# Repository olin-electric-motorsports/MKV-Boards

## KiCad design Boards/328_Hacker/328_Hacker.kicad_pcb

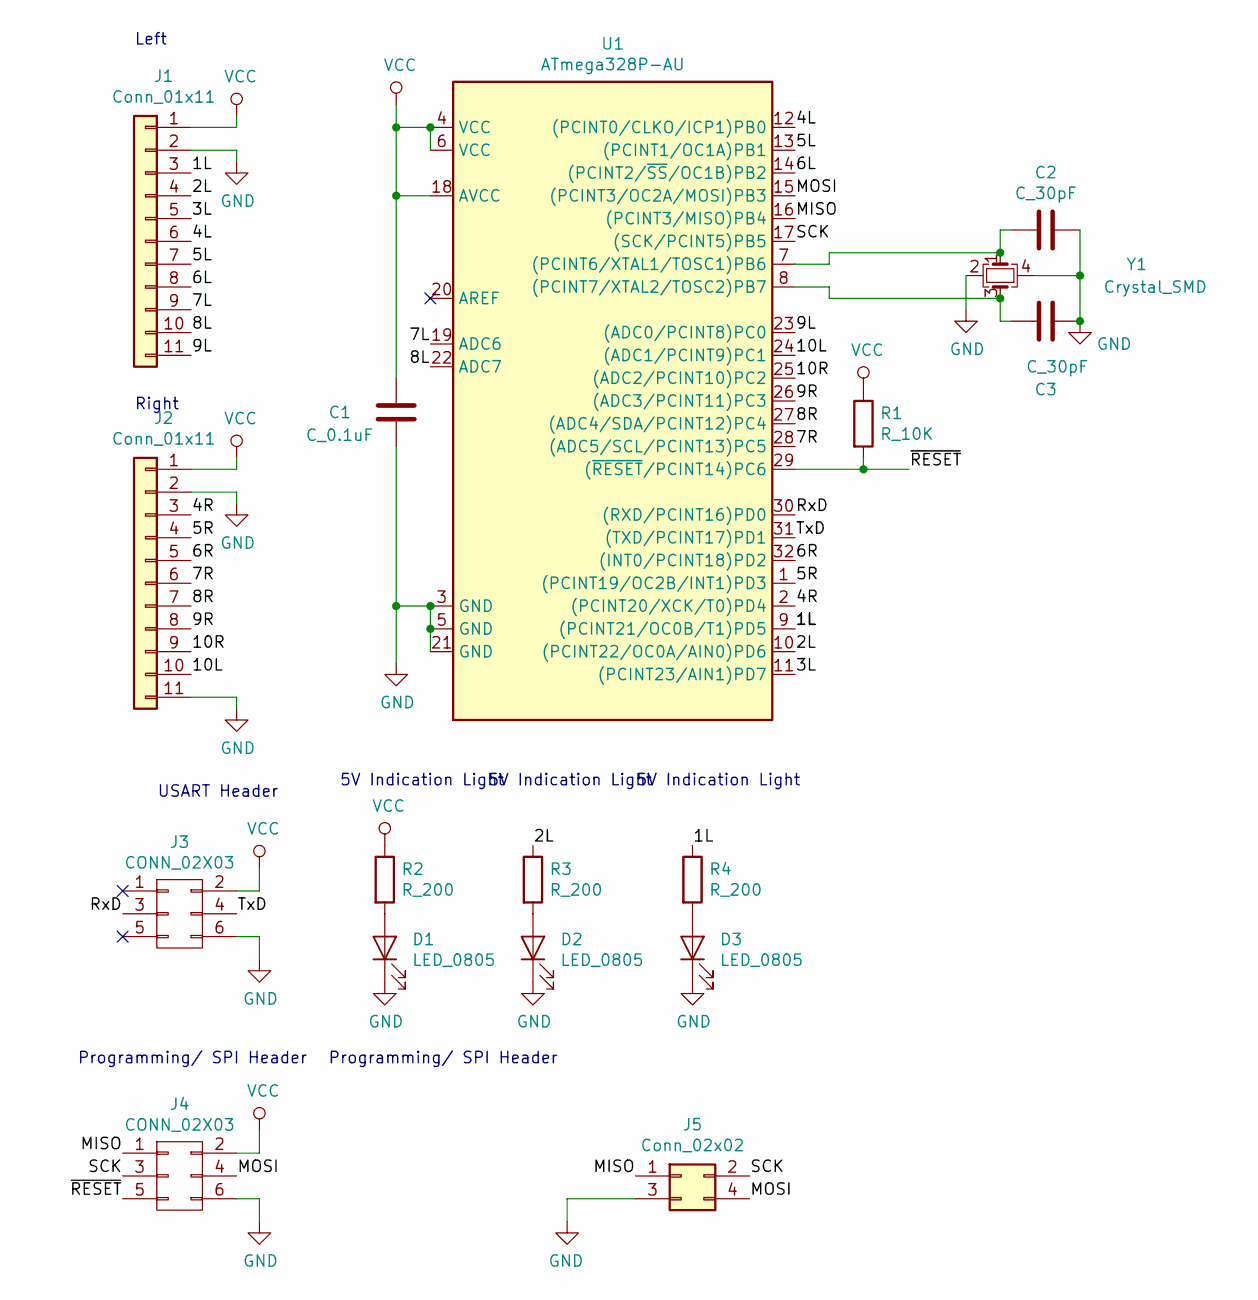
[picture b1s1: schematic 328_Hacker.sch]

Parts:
C1: C_0.1uF; C_0805_OEM; MPN 478-3352-1-ND
C2, C3: C_30pF; C_0805_OEM; MPN 1276-1130-1-ND
D1, D2, D3: LED_0805; LED_0805_OEM; MPN 475-1410-1-ND
J1, J2: Conn_01x11; PinHeader_1x11_P2.54mm_Vertical
J3, J4: CONN_02X03; Pin_Header_Straight_2x03; MPN 609-3234-ND
J5: Conn_02x02; PinSocket_2x02_P2.54mm_Vertical
R1: R_10K; R_0805_OEM; MPN CRS0805-FX-1002ELFCT-ND
R2, R3, R4: R_200; R_0805_OEM; MPN RMCF0805JT200RCT-ND
U1: ATmega328P-AU; TQFP-32_7x7mm_P0.8mm
Y1: Crystal_SMD; Crystal_SMD_FA238; MPN 887-1125-1-ND

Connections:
/1L: J1.3, R4.1, U1.9 ((PCINT21/OC0B/T1)PD5)
/2L: J1.4, R3.1, U1.10 ((PCINT22/OC0A/AIN0)PD6)
/3L: J1.5, U1.11 ((PCINT23/AIN1)PD7)
/4L: J1.6, U1.12 ((PCINT0/CLKO/ICP1)PB0)
/4R: J2.3, U1.2 ((PCINT20/XCK/T0)PD4)
/5L: J1.7, U1.13 ((PCINT1/OC1A)PB1)
/5R: J2.4, U1.1 ((PCINT19/OC2B/INT1)PD3)
/6L: J1.8, U1.14 ((PCINT2/~SS~/OC1B)PB2)
/6R: J2.5, U1.32 ((INT0/PCINT18)PD2)
/7L: J1.9, U1.19 (ADC6)
/7R: J2.6, U1.28 ((ADC5/SCL/PCINT13)PC5)
/8L: J1.10, U1.22 (ADC7)
/8R: J2.7, U1.27 ((ADC4/SDA/PCINT12)PC4)
/9L: J1.11, U1.23 ((ADC0/PCINT8)PC0)
/9R: J2.8, U1.26 ((ADC3/PCINT11)PC3)
/10L: J2.10, U1.24 ((ADC1/PCINT9)PC1)
/10R: J2.9, U1.25 ((ADC2/PCINT10)PC2)
/MISO: J4.1, J5.1, U1.16 ((PCINT3/MISO)PB4)
/MOSI: J4.4, J5.4, U1.15 ((PCINT3/OC2A/MOSI)PB3)
/RxD: J3.3, U1.30 ((RXD/PCINT16)PD0)
/SCK: J4.3, J5.2, U1.17 ((SCK/PCINT5)PB5)
/TxD: J3.4, U1.31 ((TXD/PCINT17)PD1)
/~RESET: J4.5, R1.2, U1.29 ((~RESET~/PCINT14)PC6)
GND: C1.1, C2.1, C3.1, D1.1 (K), D2.1 (K), D3.1 (K), J1.2, J2.2, J2.11, J3.6, J4.6, J5.3, U1.3 (GND), U1.5 (GND), U1.21 (GND), Y1.2, Y1.4
unnamed: C2.2, U1.7 ((PCINT6/XTAL1/TOSC1)PB6), Y1.1
unnamed: C3.2, U1.8 ((PCINT7/XTAL2/TOSC2)PB7), Y1.3
unnamed: D1.2 (A), R2.2
unnamed: D2.2 (A), R3.2
unnamed: D3.2 (A), R4.2
VCC: C1.2, J1.1, J2.1, J3.2, J4.2, R1.1, R2.1, U1.4 (VCC), U1.6 (VCC), U1.18 (AVCC)

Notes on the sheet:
USART Header
Programming/ SPI Header
Left
Right
5V Indication Light

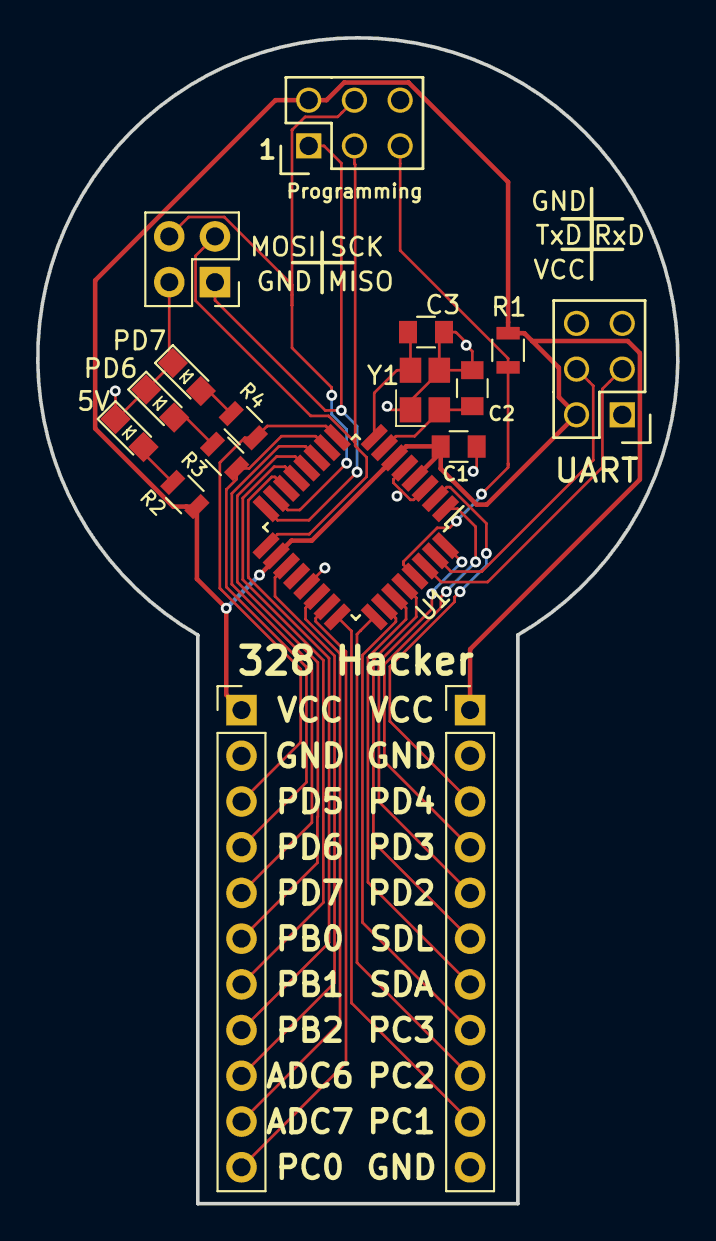
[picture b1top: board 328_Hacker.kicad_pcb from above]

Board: 2 copper layers, 35.6 x 64.8 mm, 17 parts (0 on the bottom side), 30 nets.

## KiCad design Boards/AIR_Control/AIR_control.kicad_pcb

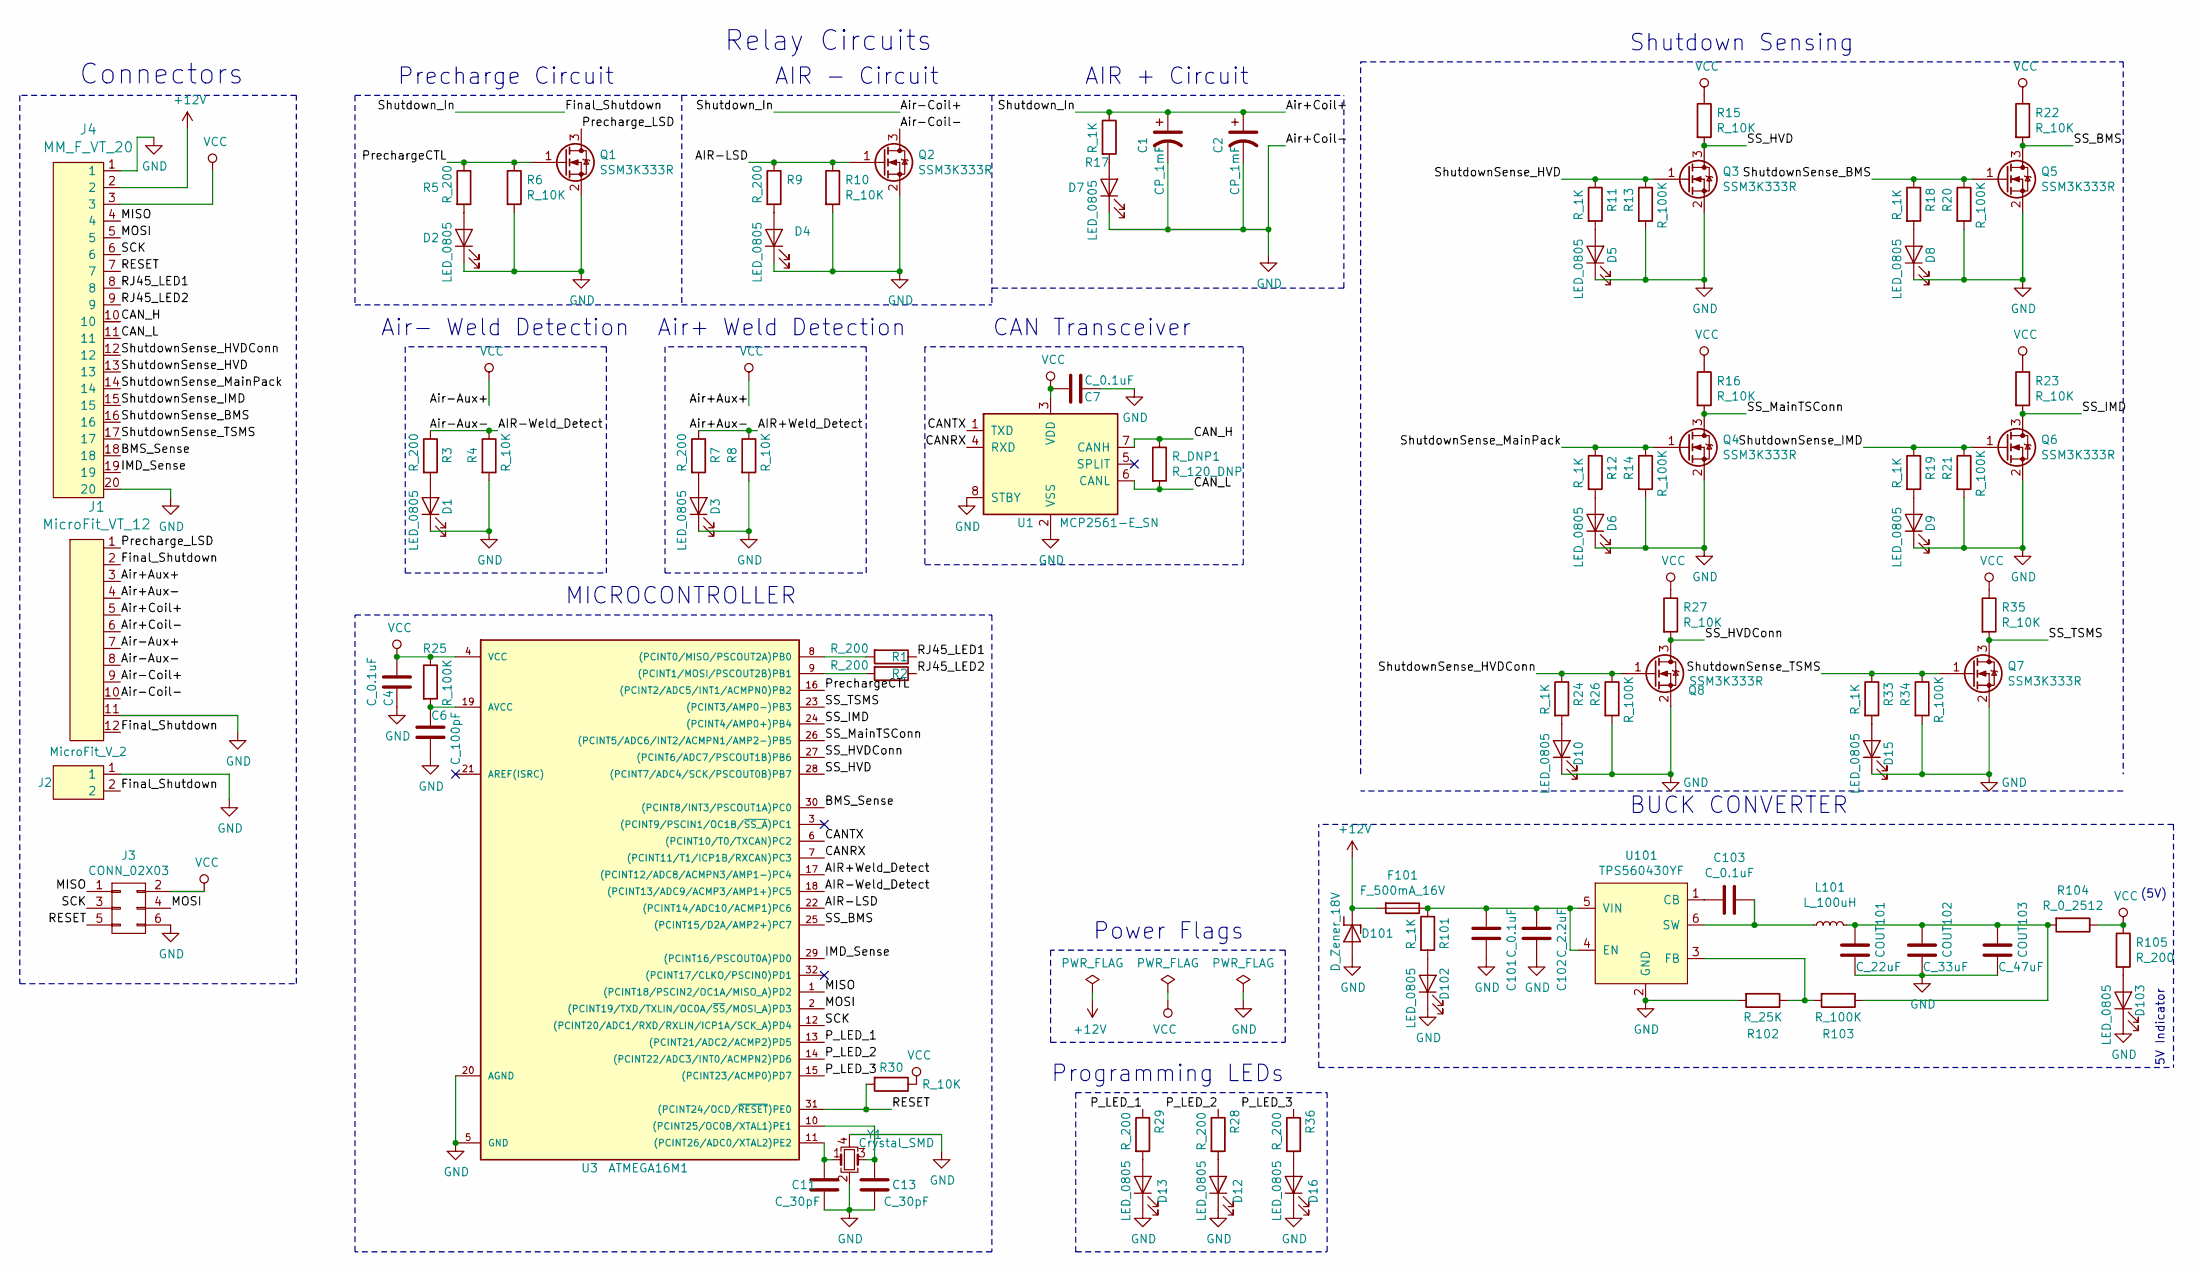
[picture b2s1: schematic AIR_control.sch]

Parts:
C1, C2: CP_1mF; C_Radial_D10_L13_P5_OEM; MPN 493-1305-ND
C4, C7, C101, C103: C_0.1uF; C_0805_OEM; MPN 478-3352-1-ND
C6: C_100pF; C_0805_OEM; MPN 732-7852-1-ND
C11, C13: C_30pF; C_0805_OEM; MPN 1276-1130-1-ND
C102: C_2.2uF; C_0603_1608Metric; MPN 311-1451-1-ND
COUT101: C_22uF; C_1206_OEM; MPN 445-11693-1-ND
COUT102: C_33uF; C_1812_OEM; MPN 445-3924-1-ND
COUT103: C_47uF; C_0805_OEM; MPN 1276-6467-1-ND
D1, D2, D3, D4, D5, D6, D7, D8, D9, D10, D12, D13, D15, D16, D102, D103: LED_0805; LED_0805_OEM; MPN 475-1410-1-ND
D101: D_Zener_18V; DO-214AA; MPN SMBJ5355B-TPMSCT-ND
F101: F_500mA_16V; Fuse_1210; MPN 507-1786-1-ND
J1: MicroFit_VT_12
J2: MicroFit_V_2; MPN WM10660-ND
J3: CONN_02X03; Pin_Header_Straight_2x03; MPN 609-3234-ND
J4: MM_F_VT_20; micromatch_female_vert_20; MPN 2-338068-0
L101: L_100uH; MPN 445-15759-1-ND
Q1, Q2, Q3, Q4, Q5, Q6, Q7, Q8: SSM3K333R; SOT-23F; MPN SSM3K333RLFCT-ND
R1, R2, R3, R5, R7, R9, R28, R29, R36, R105: R_200; R_0805_OEM; MPN RMCF0805JT200RCT-ND
R4, R6, R8, R10, R15, R16, R22, R23, R27, R30, R35: R_10K; R_0805_OEM; MPN CRS0805-FX-1002ELFCT-ND
R11, R12, R17, R18, R19, R24, R33, R101: R_1K; R_0805_OEM; MPN RNCP0805FTD1K00CT-ND
R13, R14, R20, R21, R25, R26, R34, R103: R_100K; R_0805_OEM; MPN P100KCCT-ND
R102: R_25K; R_0805_OEM; Digi-key Part Number CPF-A-0805B25KE
R104: R_0_2512; R_2512_OEM; MPN A121322CT-ND
R_DNP1: R_120_DNP; R_0805_OEM; MPN 667-ERJ-6ENF1200V
U1: MCP2561-E_SN; SOIC-8_3.9x4.9mm_Pitch1.27mm_OEM; MPN MCP2561-E/SN-ND
U3: ATMEGA16M1; TQFP-32_7x7mm_Pitch0.8mm; MPN ATMEGA16M1-AU-ND
U101: TPS560430YF; SOT-23-6_Handsoldering; MPN TPS560430YFDBVR
Y1: Crystal_SMD; Crystal_SMD_FA238; MPN 887-1125-1-ND

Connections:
+12V: D101.1 (K), F101.2, J4.2
/AIR+Weld_Detect: J1.4, R7.1, R8.1, U3.17 ((PCINT12/ADC8/ACMPN3/AMP1-)PC4)
/AIR-LSD: Q2.1 (G), R9.1, R10.1, U3.22 ((PCINT14/ADC10/ACMP1)PC6)
/AIR-Weld_Detect: J1.8, R3.1, R4.1, U3.18 ((PCINT13/ADC9/ACMP3/AMP1+)PC5)
/Air+Coil+: C1.1, C2.1, J1.2, J1.5, J1.9, J1.12, J2.2, R17.1
/Air-Coil-: J1.10, Q2.3 (D)
/BMS_Sense: J4.18, U3.30 ((PCINT8/INT3/PSCOUT1A)PC0)
/CANRX: U1.4 (RXD), U3.7 ((PCINT11/T1/ICP1B/RXCAN)PC3)
/CANTX: U1.1 (TXD), U3.6 ((PCINT10/T0/TXCAN)PC2)
/CAN_H: J4.10, R_DNP1.1, U1.7 (CANH)
/CAN_L: J4.11, R_DNP1.2, U1.6 (CANL)
/IMD_Sense: J4.19, U3.29 ((PCINT16/PSCOUT0A)PD0)
/MISO: J3.1, J4.4, U3.1 ((PCINT18/PSCIN2/OC1A/MISO_A)PD2)
/MOSI: J3.4, J4.5, U3.2 ((PCINT19/TXD/TXLIN/OC0A/~SS~/MOSI_A)PD3)
/P_LED_1: R29.1, U3.13 ((PCINT21/ADC2/ACMP2)PD5)
/P_LED_2: R28.1, U3.14 ((PCINT22/ADC3/INT0/ACMPN2)PD6)
/P_LED_3: R36.1, U3.15 ((PCINT23/ACMP0)PD7)
/PrechargeCTL: Q1.1 (G), R5.1, R6.1, U3.16 ((PCINT2/ADC5/INT1/ACMPN0)PB2)
/Precharge_LSD: J1.1, Q1.3 (D)
/RESET: J3.5, J4.7, R30.2, U3.31 ((PCINT24/OCD/~RESET~)PE0)
/RJ45_LED1: J4.8, R1.1
/RJ45_LED2: J4.9, R2.1
/SCK: J3.3, J4.6, U3.12 ((PCINT20/ADC1/RXD/RXLIN/ICP1A/SCK_A)PD4)
/SS_BMS: Q5.3 (D), R22.2, U3.25 ((PCINT15/D2A/AMP2+)PC7)
/SS_HVD: Q3.3 (D), R15.2, U3.28 ((PCINT7/ADC4/SCK/PSCOUT0B)PB7)
/SS_HVDConn: Q8.3 (D), R27.2, U3.27 ((PCINT6/ADC7/PSCOUT1B)PB6)
/SS_IMD: Q6.3 (D), R23.2, U3.24 ((PCINT4/AMP0+)PB4)
/SS_MainTSConn: Q4.3 (D), R16.2, U3.26 ((PCINT5/ADC6/INT2/ACMPN1/AMP2-)PB5)
/SS_TSMS: Q7.3 (D), R35.2, U3.23 ((PCINT3/AMP0-)PB3)
/ShutdownSense_BMS: J4.16, Q5.1 (G), R18.1, R20.1
/ShutdownSense_HVD: J4.13, Q3.1 (G), R11.1, R13.1
/ShutdownSense_HVDConn: J4.12, Q8.1 (G), R24.1, R26.1
/ShutdownSense_IMD: J4.15, Q6.1 (G), R19.1, R21.1
/ShutdownSense_MainPack: J4.14, Q4.1 (G), R12.1, R14.1
/ShutdownSense_TSMS: J4.17, Q7.1 (G), R33.1, R34.1
GND: C1.2, C2.2, C4.2, C6.2, C7.1, C11.2, C13.2, C101.2, C102.2, COUT101.2, COUT102.2, COUT103.2, D1.1 (K), D2.1 (K), D3.1 (K), D4.1 (K), D5.1 (K), D6.1 (K), D7.1 (K), D8.1 (K), D9.1 (K), D10.1 (K), D12.1 (K), D13.1 (K), D15.1 (K), D16.1 (K), D101.2 (A), D102.1 (K), D103.1 (K), J1.6, J1.11, J2.1, J3.6, J4.1, J4.20, Q1.2 (S), Q2.2 (S), Q3.2 (S), Q4.2 (S), Q5.2 (S), Q6.2 (S), Q7.2 (S), Q8.2 (S), R4.2, R6.2, R8.2, R10.2, R13.2, R14.2, R20.2, R21.2, R26.2, R34.2, R102.2, U1.2 (VSS), U1.8 (STBY), U3.5 (GND), U3.20 (AGND), U101.2 (GND), Y1.2, Y1.4; also elsewhere on the board
unnamed: C6.1, R25.2, U3.19 (AVCC)
unnamed: C11.1, U3.11 ((PCINT26/ADC0/XTAL2)PE2), Y1.1
unnamed: C13.1, U3.10 ((PCINT25/OC0B/XTAL1)PE1), Y1.3
unnamed: C101.1, C102.1, F101.1, R101.1, U101.4 (EN), U101.5 (VIN)
unnamed: C103.1, L101.1, U101.6 (SW)
unnamed: C103.2, U101.1 (CB)
unnamed: COUT101.1, COUT102.1, COUT103.1, L101.2, R103.1, R104.2
unnamed: D1.2 (A), R3.2
unnamed: D2.2 (A), R5.2
unnamed: D3.2 (A), R7.2
unnamed: D4.2 (A), R9.2
unnamed: D5.2 (A), R11.2
unnamed: D6.2 (A), R12.2
unnamed: D7.2 (A), R17.2
unnamed: D8.2 (A), R18.2
unnamed: D9.2 (A), R19.2
unnamed: D10.2 (A), R24.2
unnamed 53: D12.2 (A), R28.2; also elsewhere on the board
unnamed 54: D13.2 (A), R29.2; also elsewhere on the board
unnamed: D15.2 (A), R33.2
unnamed 56: D16.2 (A), R36.2; also elsewhere on the board
unnamed 57: D102.2 (A), R101.2; also elsewhere on the board
unnamed 58: D103.2 (A), R105.2; also elsewhere on the board
unnamed: R1.2, U3.8 ((PCINT0/MISO/PSCOUT2A)PB0)
unnamed: R2.2, U3.9 ((PCINT1/MOSI/PSCOUT2B)PB1)
unnamed: R102.1, R103.2, U101.3 (FB)
VCC: C4.1, C7.2, J1.3, J1.7, J3.2, J4.3, R15.1, R16.1, R22.1, R23.1, R25.1, R27.1, R30.1, R35.1, R104.1, R105.1, U1.3 (VDD), U3.4 (VCC)

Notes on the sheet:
Connectors
Relay Circuits
BUCK CONVERTER
5V Indicator
(5V)
MICROCONTROLLER
CAN Transceiver
Power Flags
Programming LEDs
Air+ Weld Detection
AIR + Circuit
AIR - Circuit
Precharge Circuit
Shutdown Sensing
Air- Weld Detection

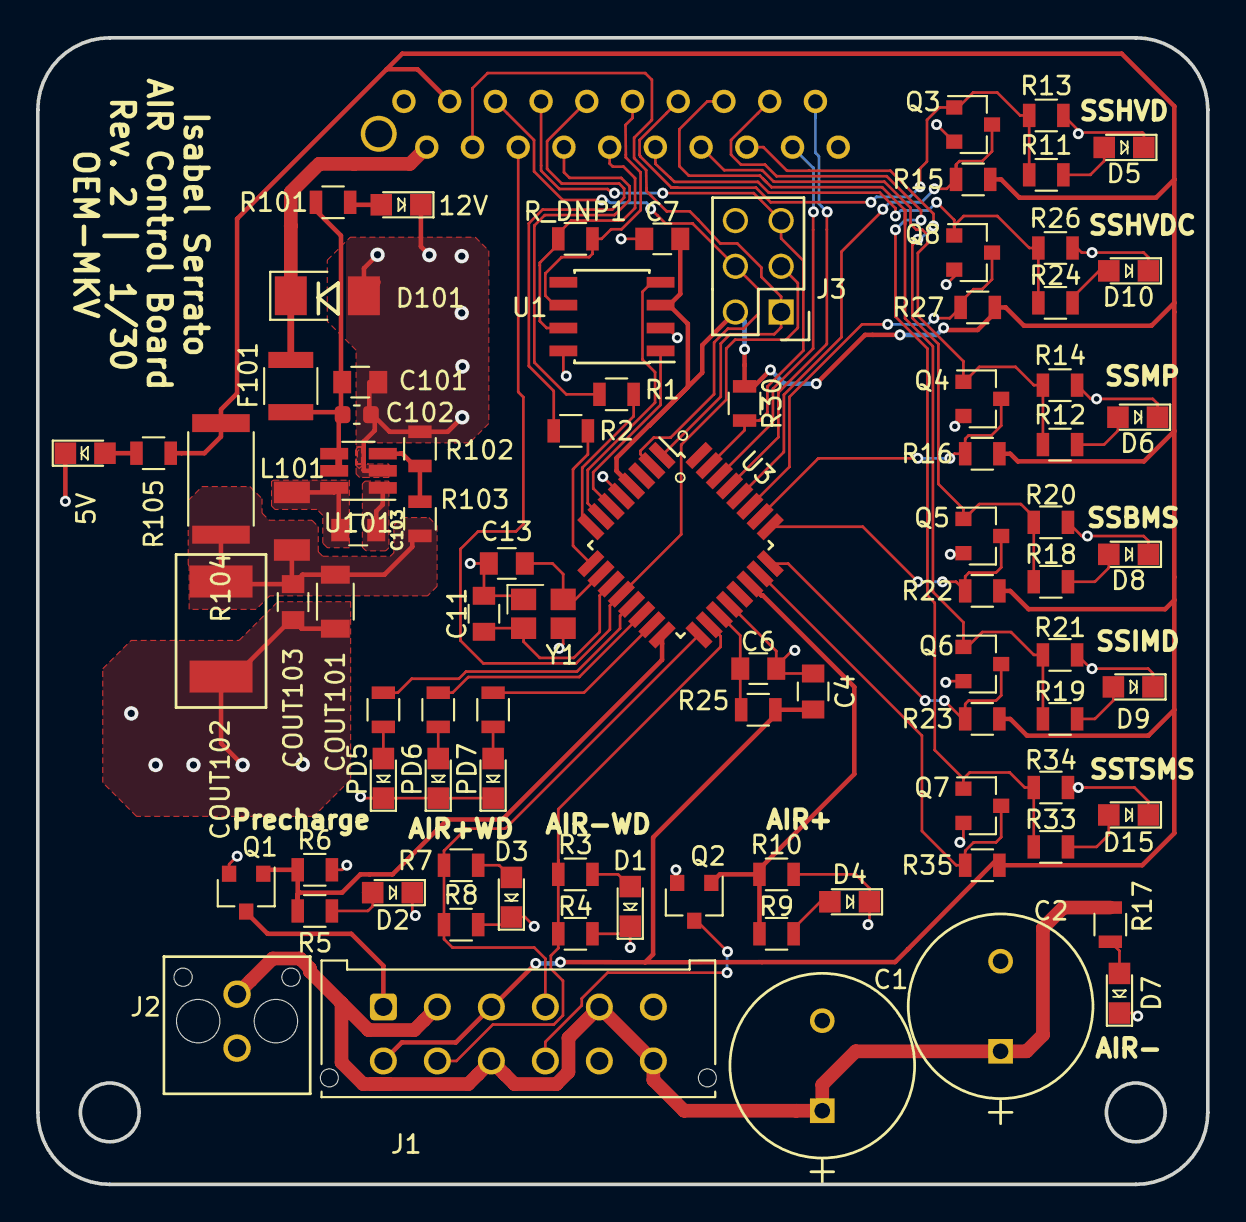
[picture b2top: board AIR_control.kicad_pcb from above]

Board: 2 copper layers, 65.0 x 63.7 mm, 88 parts (1 on the bottom side), 63 nets.

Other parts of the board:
5V, 12V: LED_0805; LED_0805_OEM
PD5, PD6, PD7: LED_0805; LED_0805_OEM

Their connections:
GND: 5V.1, 12V.1, PD5.1, PD6.1, PD7.1; also elsewhere on the board
unnamed 53: PD6.2; also elsewhere on the board
unnamed 54: PD5.2; also elsewhere on the board
unnamed 56: PD7.2; also elsewhere on the board
unnamed 57: 12V.2; also elsewhere on the board
unnamed 58: 5V.2; also elsewhere on the board

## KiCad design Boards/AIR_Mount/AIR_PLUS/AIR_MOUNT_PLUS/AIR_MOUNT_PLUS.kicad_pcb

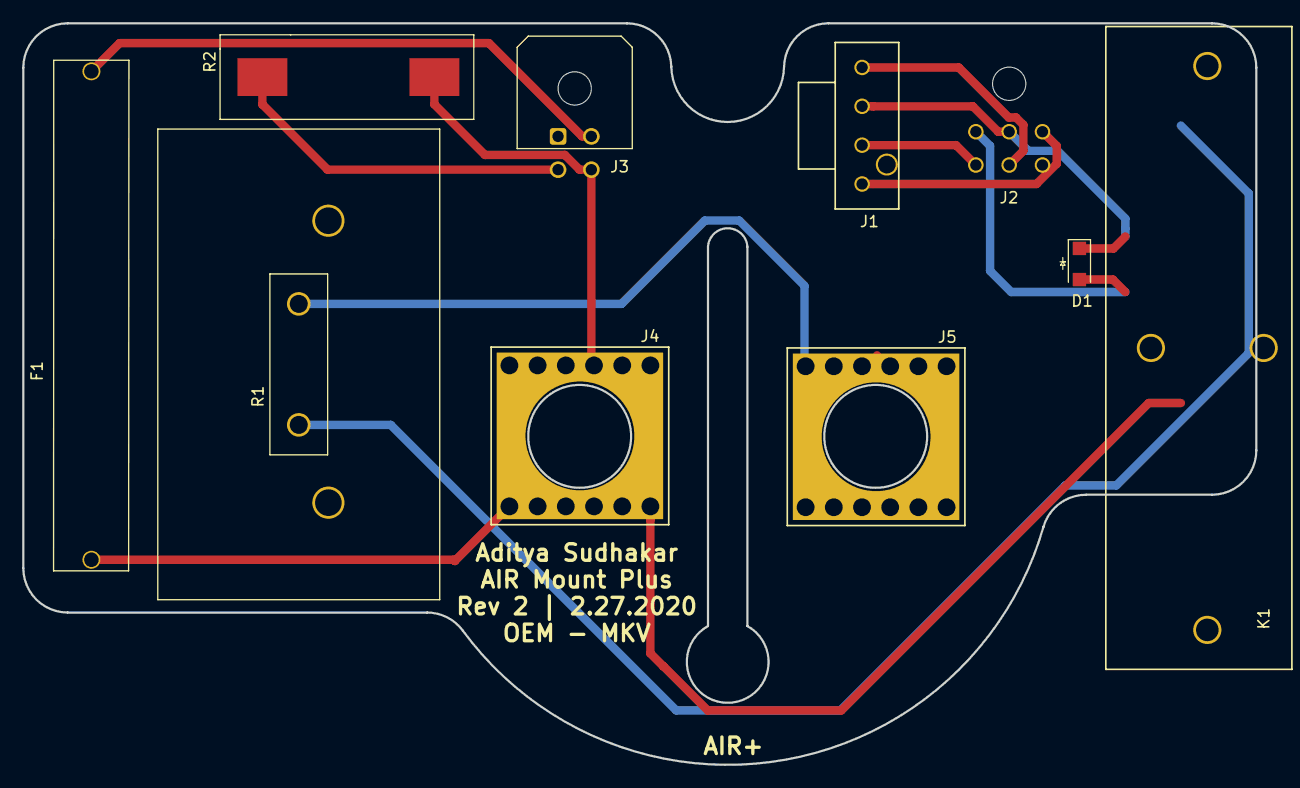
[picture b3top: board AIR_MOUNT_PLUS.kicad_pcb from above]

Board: 2 copper layers, 111.1 x 66.8 mm, 10 parts (0 on the bottom side), 10 nets.

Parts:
D1: SS110LW; D_SOD-123W_OEM
F1: F_1A_600V; Fuse_1A_600V
J1: UF_4_VT; Ultrafit_4
J2: MicroFit_RA_06
J3: MicroFit_RA_4
J4, J5: redcude_7461166; redcube_7461166
K1: DBR71210(NC); D-Series_Cynergy_Relay
R1: R_3K_HS; R_3k_HS_TO247
R2: R_10K_HV; R_TSMP_SMD_5329

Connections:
/AUX+: J1.1, J2.3
/AUX-: J1.2, J2.4
/BAT-: J5.1, R1.1
/Coil+: D1.1, J1.3, J2.2, K1.4
/Coil-: J1.4, J2.5
/GND: D1.2, J2.1, K1.3
/TS-: F1.1, J3.4, J4.1, K1.1, R2.2
/TSMP-: J3.3, R2.1
/TS_Fused-: F1.2, J3.2
unnamed: K1.2, R1.2

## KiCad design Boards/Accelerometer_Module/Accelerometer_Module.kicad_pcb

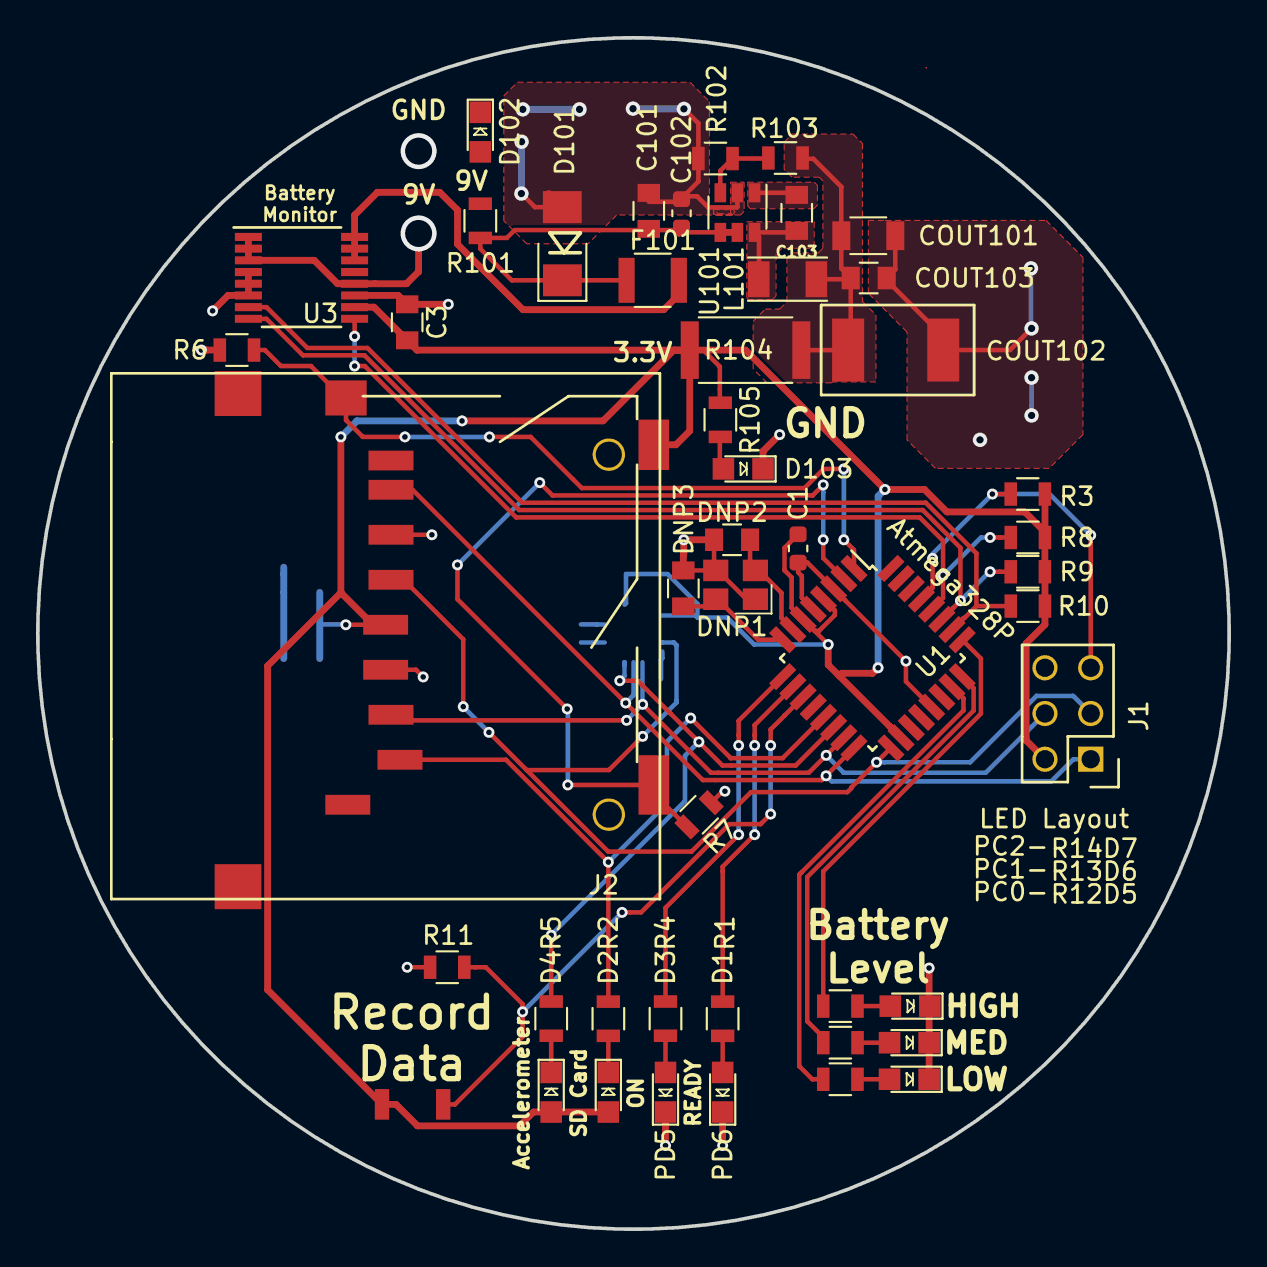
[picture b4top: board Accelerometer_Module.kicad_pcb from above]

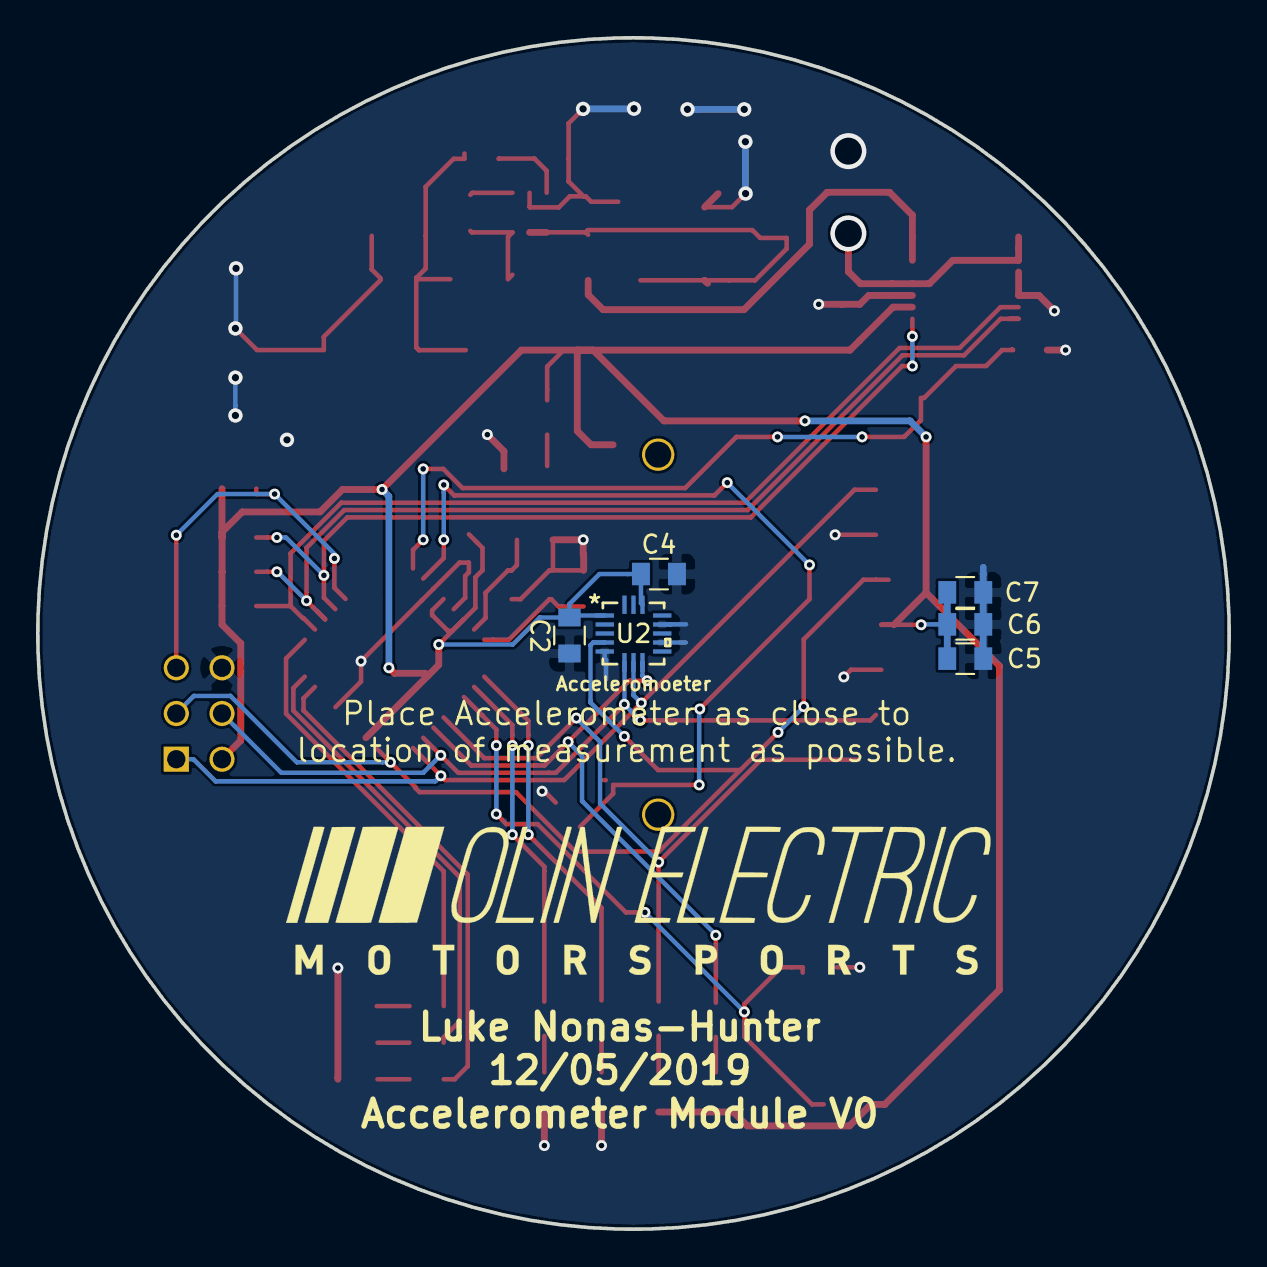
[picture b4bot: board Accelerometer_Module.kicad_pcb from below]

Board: 2 copper layers, 66.2 x 66.2 mm, 54 parts (6 on the bottom side), 37 nets.

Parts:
C1: C_100nF; C_0603_1608Metric
C2, C5: C_10uF; C_0805_OEM
C3, C4, C7, C101, C103: C_0.1uF; C_0805_OEM
C6: C_1uF; C_0805_OEM
C102: C_4.7uF; C_0603_1608Metric
COUT101: C_22uF; C_1206_OEM
COUT102: C_33uF; Fuse_1812
COUT103: C_47uF; C_0805_OEM
D1, D2, D4: LED_0805_Red; LED_0805_OEM
D3, D5, D6, D7, D102, D103: LED_0805; LED_0805_OEM
D101: D_Zener_18V; DO-214AA
DNP1: Crystal_SMD; Crystal_SMD_FA238
DNP2, DNP3: C_30pF; C_0805_OEM
F101: F_500mA_16V; Fuse_1210
J1: CONN_02X03; Pin_Header_Straight_2x03
J2: SD_socket; sd_socket_molex_5009980900
L101: L_15uH; L_100uH_OEM
R1, R2, R4, R5, R12, R13, R14, R105: R_100; R_0805_OEM
R3, R6, R7, R8, R9, R10, R11: R_10K; R_0805_OEM
R101: R_499; R_0805_OEM
R102: R_25K; R_0805_OEM
R103: R_54.9K; R_0805_OEM
R104: R_0_2512; R_2512_OEM
SW1: SW_Push_SPST_NO; SW_B3U-1000P_4.2x1.7mm
U1: ATmega328P-AU; TQFP-32_7x7mm_P0.8mm
U2: LIS3DHTR
U3: INA260; TSSOP-16_4.4x5mm_P0.65mm
U101: TPS560430YF; SOT-23-6_OEM

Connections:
/9V_in: U3.1, U3.2, U3.3, U3.12
/9V_out: F101.2, U3.14, U3.15, U3.16
/ALERT: R10.2, U1.26, U3.7
/CS: R5.1, U1.14, U2.8
/CS_SD: J2.1, R2.2, U1.13
/Detect: J2.12, R7.1, U1.2
/MISO: J1.1, J2.7, U1.16, U2.7
/MOSI: J1.4, J2.2, U1.15, U2.6
/PC0: R12.1, U1.23
/PC1: R13.1, U1.24
/PC2: R14.1, U1.25
/Protect: J2.11, R6.1, U1.1
/RESET: J1.5, R3.2, U1.29
/SCK: J1.3, J2.5, U1.17, U2.4
/SCL: R8.2, U1.28, U3.9
/SDA: R9.2, U1.27, U3.8
GND: C1.1, C2.1, C3.1, C4.2, C5.2, C6.2, C7.2, C101.2, C102.2, COUT101.2, COUT102.2, COUT103.2, D1.1, D3.1, D5.1, D6.1, D7.1, D101.2, D102.1, D103.1, DNP1.2, DNP1.4, DNP2.2, DNP3.2, J1.6, J2.3, J2.6, R6.2, R7.2, R11.2, R102.2, U1.3, U1.5, U1.21, U2.5, U2.10, U2.12, U3.4, U3.5, U3.6, U3.11, U101.2
unnamed: C101.1, C102.1, D101.1, F101.1, R101.1, U101.4, U101.5
unnamed: C103.1, U101.1
unnamed: C103.2, L101.1, U101.6
unnamed: COUT101.1, COUT102.1, COUT103.1, L101.2, R103.1, R104.1
unnamed: D1.2, R1.2
unnamed: D2.1, R2.1
unnamed: D3.2, R4.1
unnamed: D4.1, R5.2
unnamed: D5.2, R12.2
unnamed: D6.2, R13.2
unnamed: D7.2, R14.2
unnamed: D102.2, R101.2
unnamed: D103.2, R105.2
unnamed: DNP1.1, DNP2.1, U1.7
unnamed: DNP1.3, DNP3.1, U1.8
unnamed: R1.1, U1.10
unnamed: R4.2, U1.9
unnamed: R11.1, SW1.1, U1.11
unnamed: R102.1, R103.2, U101.3
VCC: C1.2, C2.2, C3.2, C4.1, C5.1, C6.1, C7.1, D2.2, D4.2, J1.2, J2.4, J2.10, R3.1, R8.1, R9.1, R10.1, R104.2, R105.1, SW1.2, U1.4, U1.6, U1.18, U2.1, U2.14, U3.10

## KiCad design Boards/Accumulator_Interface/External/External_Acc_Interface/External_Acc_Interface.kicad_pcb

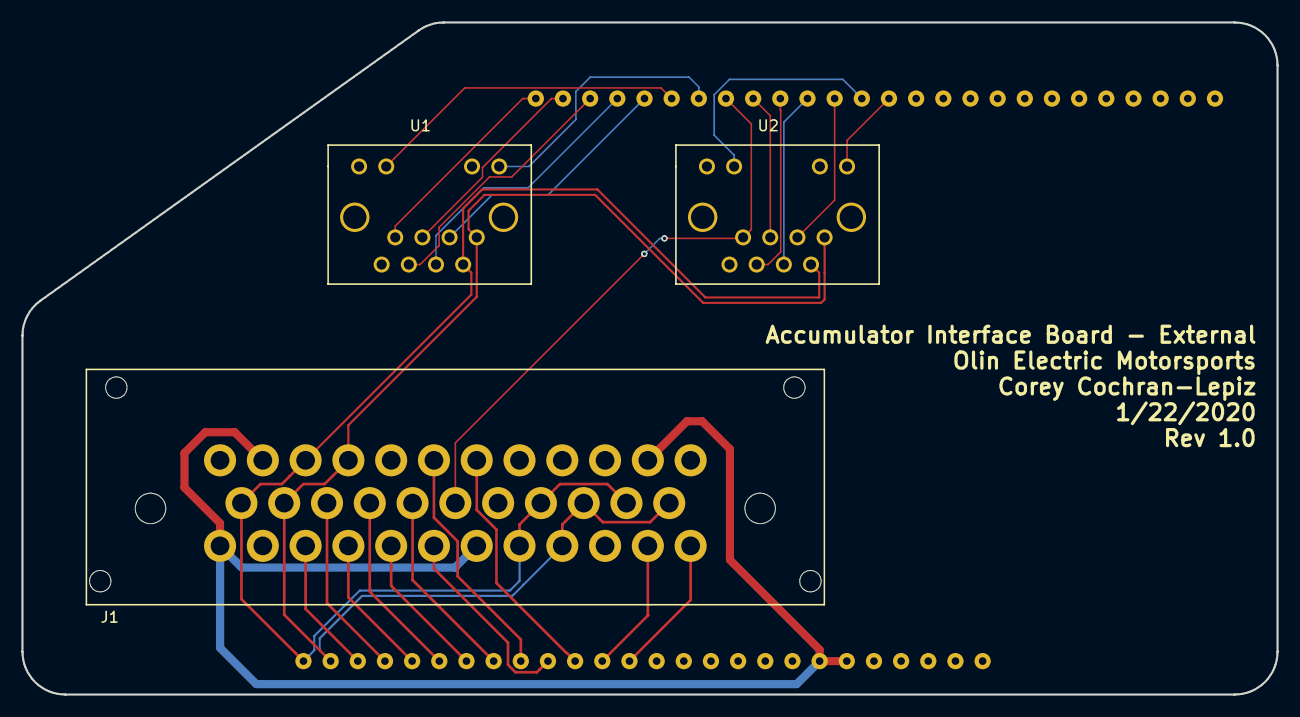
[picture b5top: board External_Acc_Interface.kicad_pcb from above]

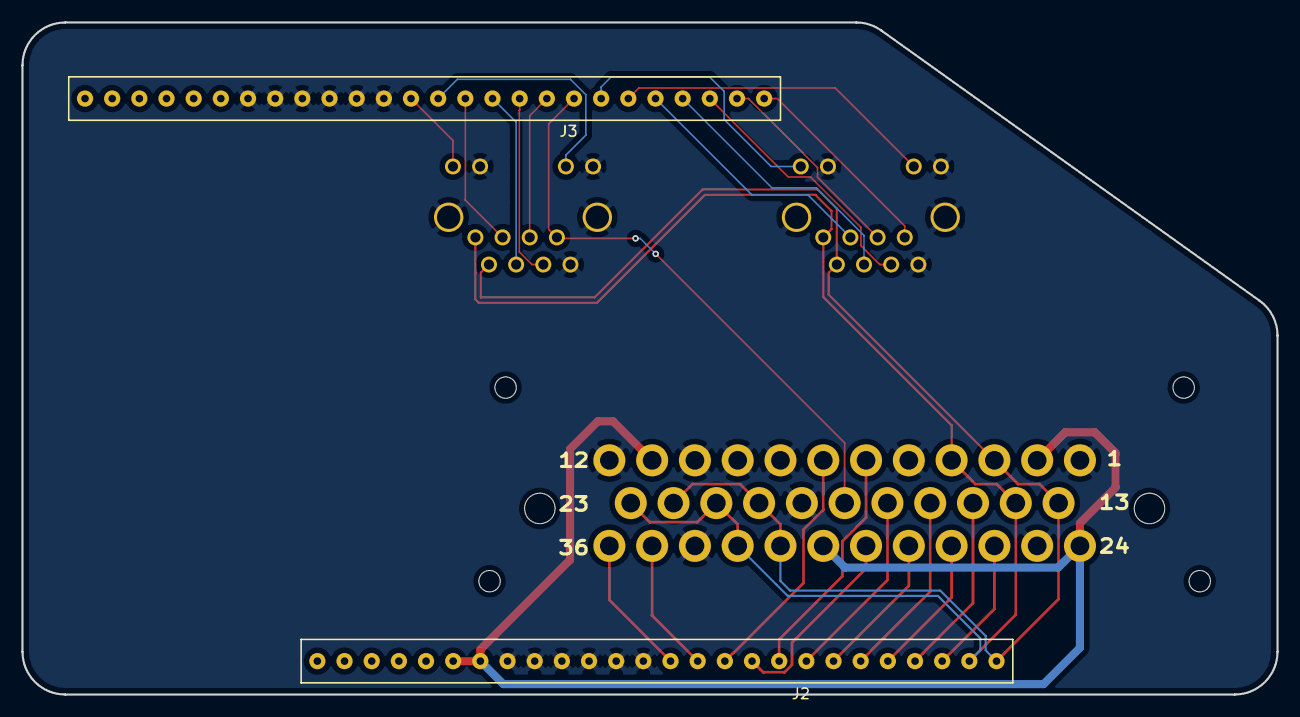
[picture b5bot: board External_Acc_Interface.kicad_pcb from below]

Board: 2 copper layers, 117.4 x 62.8 mm, 5 parts (2 on the bottom side), 29 nets.

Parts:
J1: Ampseal_35_VT; Ampseal_35
J2: SS-126-G-2; 26pos_screwsocket_.1in
J3: BBS-126-G-A; 26pos_screwsocket_.1in
U1, U2: RJ45_VT; RJ45-Vertical

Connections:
/5V_AIRC: J1.18, J3.8, U2.7
/5V_BMS: J3.1, U1.7
/12V: J1.2, J1.11, J1.24, J1.30, J2.20, J2.21
/BSDP-Current-Sense: J1.34, J2.12
/CAN-GND: J1.1, J1.5, J1.8, J1.9, J1.10, J1.12, J1.19, J1.25, J1.33, J2.14, J2.15, J2.16, J2.17, J2.18, J2.19, J3.15, J3.16, J3.17, J3.18, J3.19, J3.20, U1.8, U1.9, U1.11, U1.13, U1.14, U2.8, U2.9, U2.11, U2.13, U2.14
/CAN_N: J1.4, J1.14, J1.21, J1.23, J1.32, J2.2, U1.1, U2.1
/CAN_P: J1.3, J1.13, J1.20, J1.22, J1.31, J2.1, U1.2, U2.2
/ChargeEnable1: J1.28, J2.7
/ChargeEnable2: J1.29, J2.10
/FAN-PWM: J1.17, J2.8
/HVD->HVD-Connector: J1.35, J2.13
/IMD->TSMS: J1.6, J2.9
/LED_G_AIRC: J3.14, U2.12
/LED_G_BMS: J3.7, U1.12
/LED_O_AIRC: J3.13, U2.10
/LED_O_BMS: J3.6, U1.10
/MISO_AIRC: J3.9, U2.5
/MISO_BMS: J3.2, U1.5
/MOSI_AIRC: J3.10, U2.6
/MOSI_BMS: J3.3, U1.6
/RESET_AIRC: J3.12, U2.3
/RESET_BMS: J3.5, U1.3
/SCK_AIRC: J3.11, U2.4
/SCK_BMS: J3.4, U1.4
/TSAL-Green-Neg: J1.16, J2.6
/TSAL-Green-Pos: J1.15, J2.4
/TSAL-Red-Neg: J1.27, J2.5
/TSAL-Red-Pos: J1.26, J2.3
/TSMS->FinalShutdown: J1.7, J2.11

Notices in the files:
parts and their libraries:
Copyright 2016 Accelerated Designs. All rights reserved.
